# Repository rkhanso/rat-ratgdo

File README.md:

# My Addition
-an Eagle Schematic and PCB that is proven to work (I'm using it on my Chamberlain garage door).

My schematic/board uses a 2n7000 and a RFP30N06LE.

Controller is a generic ESP8266 D1 Mini.

There is only one 3-pin screw connector. Why do you need anything more? 

No extra dry contacts or anything. Just use this in Home Assistant and you'll be fine.

# rat-ratgdo
RAGE
AGAINST
THE
RATGDO

Credit and inspiration for this work goes to [@rlowens](https://github.com/rlowens) to let me know that there are other technical folks out there who needed this other than myself.

## Overview
This is an open source schematic for the ratgdo, based on the v2.5 [ratgdo](https://github.com/PaulWieland/ratgdo) PCB and code but installed using the [ESPHome fork](ESPHome%20vs%20native%20ratgdo.md) of ratgdo.  We feel there is cognitive dissonance between the refusal to provide (and deleting requests for) schematics for the ratgdo PCB against the ratgdo project's use of open source code, open source licensing, and libraries used by other open source projects, as well as the inception reasoning for the ratgdo project which was to ensure that nobody is at the mercy of a third party that might stop selling the PCBs.

This project was created to allow people who need a ratgdo solution for their garage door opener but either cannot, or choose not to, source the solution from Paul Wieland and be locked into that 3rd party. It also ensures that the PCB can be recreated as and when the project maintainer gives up on the project (much like Chamberlain themselves might do with their MyQ Cloud Service) and stops selling PCBs.

### You are expected to know how to create the described circuit using your own prototyping skills.  That is, this project is for people who can solder well and know how to read schematics

The PCB schematic here does not describe any circuitry other than the serial line garage door control and obstruction sensor.  All other optional features provided by ratgdo could also be reverse engineered as needed.

**If you want to buy a pre-made ratgdo setup, purchase it [from Paul Wieland](https://github.com/PaulWieland/ratgdo).**

See images of a [working breadboard prototype](images/Breadboard_working.png) and the [subsequent soldered prototype using a D1 shield](images/Simple%20prototype%20using%20D1%20shield.jpg).  Both of these prototypes are using 2n7000 MOSFETs exclusively, but that is because they are prototypes and long term reliability of data transmission when using the 2n7000 has not been confirmed.  See the section below on needed components for context.

## Components needed
This schematic assumes the use of through-hole components.  If you wish to use SMD components, please refer to the [FAQ](FAQ.md#what-if-i-want-to-use-sot-23-smd-components).

Aside from the obvious requirement of a [supported ESP-32 or ESP8266 board](Supported%20Boards.md) flashed with the [ESPHome version](https://github.com/ratgdo/esphome-ratgdo), you will need 3x 10 kohm (kilo-ohm) resistors, and two 2n7000 N-channel MOSFET (TO-92 package is easiest).  It is also recommended you aquire a suitable 3-post screw terminal and some red, white, and black wire for connecting to the door opener.  These connections are very low current, so you can get away with fairly thin wire.

**Note:** Our simple through-hole Bill Of Materials uses 2n7000 MOSFETs for both RX and TX, however depending on the manufacturere of your 2n7000 and its production batch, it might not be 100% reliable for the TX circuit.  There are many examples working using the 2n7000 however, so there is a very high chance it will work.

## INSTALL REQUIREMENTS
Due the schematics we have provided and how they are laid out, you must use the ESPHome fork of ratgdo and - for ESP8266 based boards - select the blue v2.5 board on the ESPhome [web installer page](https://ratgdo.github.io/esphome-ratgdo/).  For ESP-32 based boards the above does not currently apply and you must use the v2.0 installer and follow our ESP-32 schematic we provide in the Supported Boards page.

For the ESP8266 based boards, if installing using Paul Wieland's native ratgdo installer and you install for a v2.0 board, you must wire your TX to D4 (GPIO2) rather than D1 (GPIO5).

## Having a PCB printed
You may use the files from the [schematics folder](kicad_files) to have your own PCB printed.  Shown is an example 3D render of an ESP32 based board using a Wemos ESP32 D1 board.

_An example of the D1 Mini ESP32 Wide Format_

### Schematic options
We provide a few options of schematic files suitable for sending to a PCB printing company.  Currently provided are:
- [Wemos D1 Mini ESP8266](kicad_files/D1%20Mini%20-%20ESP8266)
- [Wemos D1 Mini ESP32](kicad_files/D1%20Mini%20-%20ESP32) (massive overkill for ratgdo but it's your choice!)
- [Wemos D1 Mini ESP32 Wide Format](kicad_files/D1%20Mini%20Wide%20-%20ESP32)
- [Bare ESP8266 module](kicad_files/Bare%20ESP8266)

> If you just want to try ordering a board from somewhere like PCBWay, then check out the most recent [build artifacts](https://github.com/Kaldek/rat-ratgdo/actions/workflows/pcb.yaml)

## How the ratgdo circuit works
The ratgdo circuitry which we cover in this project consists of two sections; Garage Door control and obstruction sensors.

### Garage Door Control
#### Description of the Chamberlain configuration
The Chamberlain garage door control circuit is a two-wire setup consisting of a Ground, and a combined +12v power and serial data line.  The serial data line is held at 12v unless data transmission is occurring.  Data transmission is performed by pulling the 12v line down to GND for each data bit.  The benefit here is that a single wire can be used for providing power to door control panels and data transmssion on a single wire.  The use of appropriately sized capacitors in door control panels means they do not switch off during data transmission.

#### How ratgdo interfaces with the Chamberlain wiring
The ratgdo taps into the red control wire and uses this single wire for transmission of commands onto the serial bus, and for receiving data from the serial bus.  As it is a single wire protocol and operates half-duplex, the ratgdo circuitry uses N-channel MOSFETs wired in a manner which allows the ESP8266 to never transmit when the serial line is already low.

In operation, this means that the ratgdo is mostly listening to the serial bus to ensure it is keeping track of the state of the door.  For example, if the door is manually opened (or opened by use of the MyQ app even), these events are broadcast onto the serial bus by the door controller.  ratgdo is therefore able to know that the state of the door has changed.  In turn, this means that when controlling ratgdo via Home Assistant, the status of the door in HA is always up to date.

#### Wiring to Garage Door

### Obstruction sensor
The ratgdo monitors the real-time state of the obstruction sensors directly.  We assume this is because obstruction status is not broadcast in real time by the door controller, and safety is paramount.  It allows you to set up real-time alerts in Home Assistant for any time the door is obstructed.  The ratgdo taps into the obstruction sensor power wire which also acts as a communication bus, however the signalling is only an ongoing status of whether the obstruction sensors are working and whether there is an obstruction.

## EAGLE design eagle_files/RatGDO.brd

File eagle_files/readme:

# Single-sided Eagle files

Download files above and open in Eagle to make your own single-sided PCBs at home.

PCB is proven to work (I'm using it on my Chamberlain garage door).

My schematic/board uses a 2n7000 and a RFP30N06LE.

Controller is a generic ESP8266 D1 Mini.

There is only one 3-pin screw connector. Why do you need anything more?

No extra dry contacts or anything. Just use this in Home Assistant and you'll be fine.

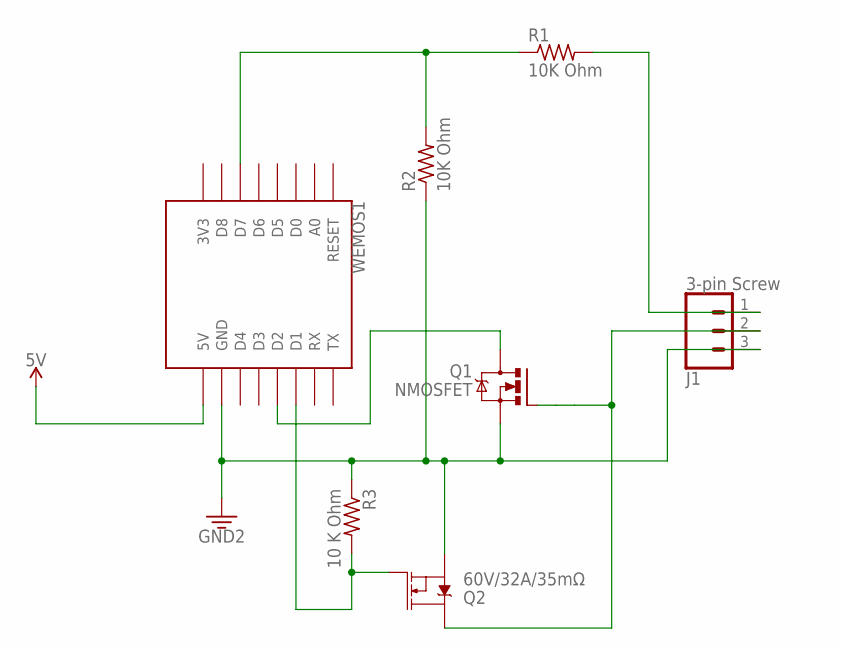
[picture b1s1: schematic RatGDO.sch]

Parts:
J1: 3-pin Screw; SCREWTERMINAL-3.5MM-3
Q1: NMOSFET; TO92
Q2: 60V/32A/35mΩ; TO220V
R1, R2: 10K Ohm; 0309/12
R3: 10 K Ohm; 0309/12
WEMOS1: WEMOS-D1-MINI

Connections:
5V: WEMOS1.5V
D1: Q2.1 (G), R3.2, WEMOS1.D1
D2: Q1.1 (D), WEMOS1.D2
D7: R1.1, R2.2, WEMOS1.D7
GND: J1.3, Q1.3 (S), Q2.3 (S), R2.1, R3.1, WEMOS1.GND
PIN1: J1.1, R1.2
PIN2: J1.2, Q1.2 (G), Q2.2 (D)

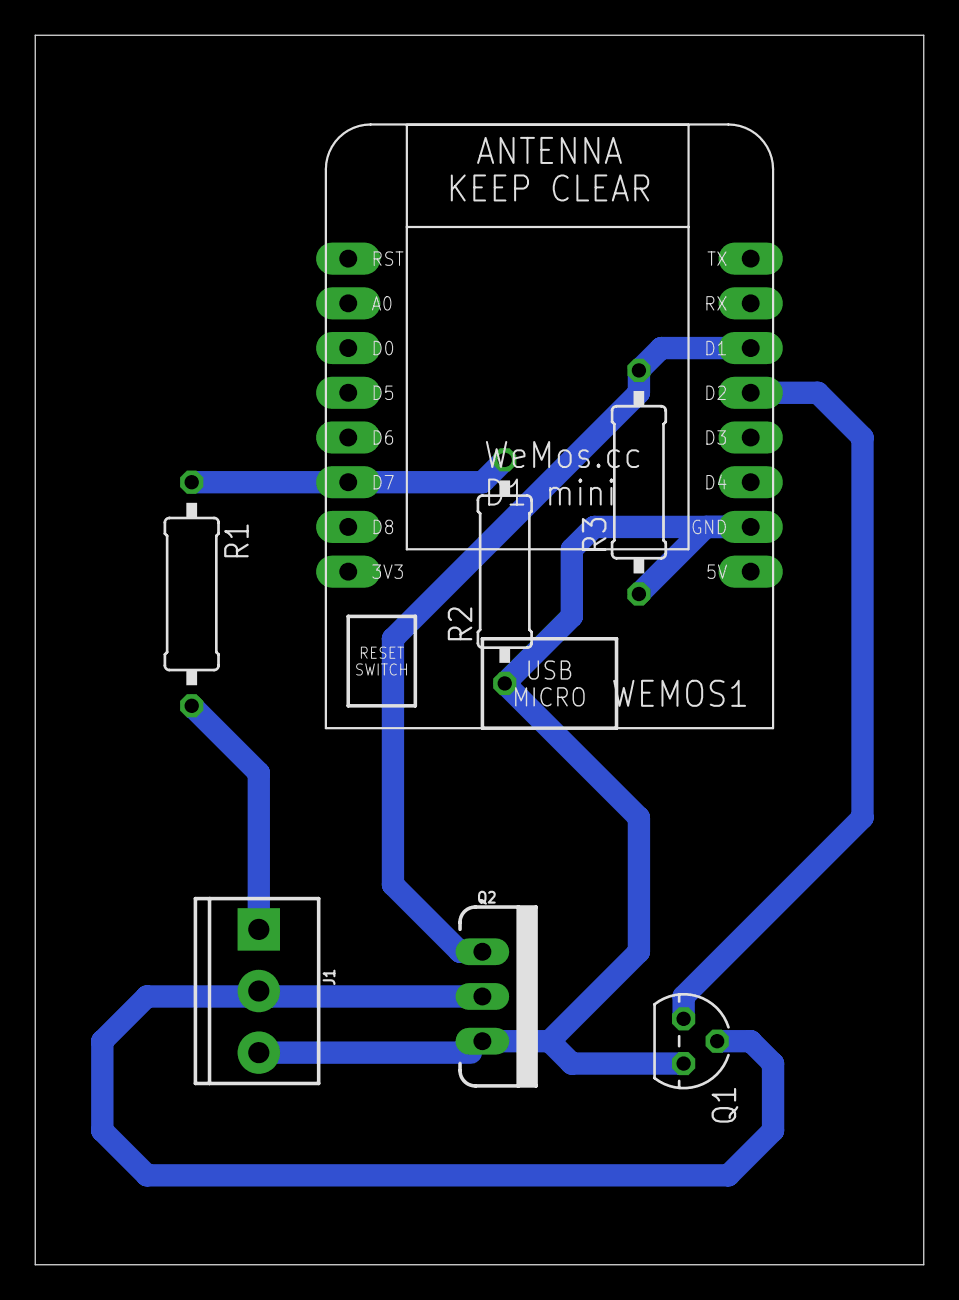
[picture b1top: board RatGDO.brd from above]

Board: 2 copper layers, 50.5 x 69.8 mm, 7 parts (0 on the bottom side), 6 nets.

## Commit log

2023-11-20 1-Sided PCB for Eagle
    I've been making 1-sided PCBs for a long time. If you'd like to make a simple board for the Ratgdo, give this a try.
    I used a 2N7000 and a RFP30N06LE transistor bought on Amazon.
    No extra connectors, just a screw terminal, 3 10K resistors, some headers and a D1 Mini and you're all set.
2023-11-20 Update README.md
    My only contribution here - an Eagle .sch and .brd file.
2023-11-20 Create test
2023-11-20 Create ESP8266_D1_Mini_Single-sided
2023-11-20 Update ESP8266_D1_Mini_Single-sided
2023-11-20 Create ESP8266_D1-Mini_single-sided
2023-11-20 Create file
2023-11-20 Create eagle_files

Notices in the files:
parts and their libraries:
SparkFun-Connectors: Licensing: Creative Commons ShareAlike 4.0 International - https://creativecommons.org/licenses/by-sa/4.0
